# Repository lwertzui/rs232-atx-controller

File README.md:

# rs232-atx-controller    
Device to start and restart Computers, controlled via rs232 through MAX232, powered by an Atmega8P, supports up to 8 computers at the same time, will probably do a version with only 4 which can also check the status of two leds

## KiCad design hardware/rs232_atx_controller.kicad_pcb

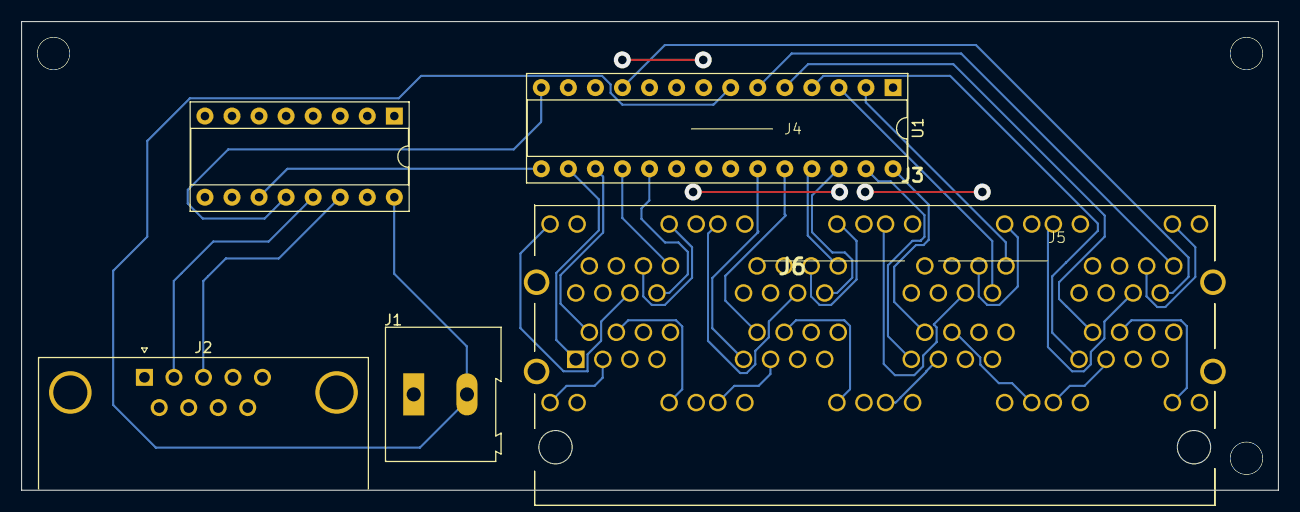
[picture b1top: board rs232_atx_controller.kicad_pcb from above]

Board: 2 copper layers, 118.0 x 44.0 mm, 5 parts (0 on the bottom side), 38 nets.

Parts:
J1: Screw_Terminal_01x02; TerminalBlock_Altech_AK300-2_P5.00mm
J2: DE9_Plug; DSUB-9_Male_Horizontal_P2.77x2.84mm_EdgePinOffset7.70mm_Hou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
J3: HCJ24-804SK-L12; HCJ24804SKL12
U1: ATmega8A-P; DIP-28_W7.62mm_Socket
U2: MAX232; DIP-16_W7.62mm_Socket

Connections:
+5V: J1.2, U1.7 (VCC), U2.16 (VCC)
GND: J1.1, J2.0, J2.5, J3.A9 (CATHODE_YELLOW_1), J3.A11 (CATHODE_YELLOW_2), J3.B10 (CATHODE_YELLOW_3), J3.B12 (CATHODE_YELLOW_4), J3.C9 (CATHODE_YELLOW_5), J3.C11 (CATHODE_YELLOW_6), J3.D10 (CATHODE_YELLOW_7), J3.D12 (CATHODE_YELLOW_8), J3.E9 (CATHODE_YELLOW_9), J3.E11 (CATHODE_YELLOW_10), J3.F10 (CATHODE_YELLOW_11), J3.F12 (CATHODE_YELLOW_12), J3.G9 (CATHODE_YELLOW_13), J3.G11 (CATHODE_YELLOW_14), J3.H10 (CATHODE_YELLOW_15), J3.H12 (CATHODE_YELLOW_16), U1.8 (GND), U2.15 (GND)
unnamed: J3.A4, J3.A10 (ANODE_GREEN_1)
unnamed: J3.A3, J3.A12 (ANODE_GREEN_2)
unnamed: J3.B4, J3.B9 (ANODE_GREEN_3)
unnamed: J3.B3, J3.B11 (ANODE_GREEN_4)
unnamed: J3.C4, J3.C10 (ANODE_GREEN_5)
unnamed: J3.C3, J3.C12 (ANODE_GREEN_6)
unnamed: J3.D4, J3.D9 (ANODE_GREEN_7)
unnamed: J3.D3, J3.D11 (ANODE_GREEN_8)
unnamed: J3.E3, J3.E10 (ANODE_GREEN_9)
unnamed: J3.E4, J3.E12 (ANODE_GREEN_10)
unnamed: J3.F4, J3.F9 (ANODE_GREEN_11)
unnamed: J3.F3, J3.F11 (ANODE_GREEN_12)
unnamed: J3.G4, J3.G10 (ANODE_GREEN_13)
unnamed: J3.G3, J3.G12 (ANODE_GREEN_14)
unnamed: J3.H4, J3.H9 (ANODE_GREEN_15)
unnamed: J3.H3, J3.H11 (ANODE_GREEN_16)
unnamed: U1.14 (PB0), U2.12 (R1OUT)
unnamed: U1.15 (PB1), U2.11 (T1IN)
unnamed: J3.A1, U1.16 (PB2)
unnamed: J3.A2, U1.17 (PB3)
unnamed: J3.B1, U1.18 (PB4)
unnamed: J3.B2, U1.19 (PB5)
unnamed: J3.C1, U1.23 (PC0)
unnamed: J3.C2, U1.24 (PC1)
unnamed: J3.D1, U1.25 (PC2)
unnamed: J3.D2, U1.26 (PC3)
unnamed: J3.E1, U1.27 (PC4)
unnamed: J3.E2, U1.28 (PC5)
unnamed: J3.F1, U1.2 (PD0)
unnamed: J3.F2, U1.3 (PD1)
unnamed: J3.G1, U1.4 (PD2)
unnamed: J3.G2, U1.5 (PD3)
unnamed: J3.H1, U1.6 (PD4)
unnamed: J3.H2, U1.11 (PD5)
unnamed: J2.2, U2.13 (R1IN)
unnamed: J2.3, U2.14 (T1OUT)

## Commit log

2025-01-05 add pcb files
